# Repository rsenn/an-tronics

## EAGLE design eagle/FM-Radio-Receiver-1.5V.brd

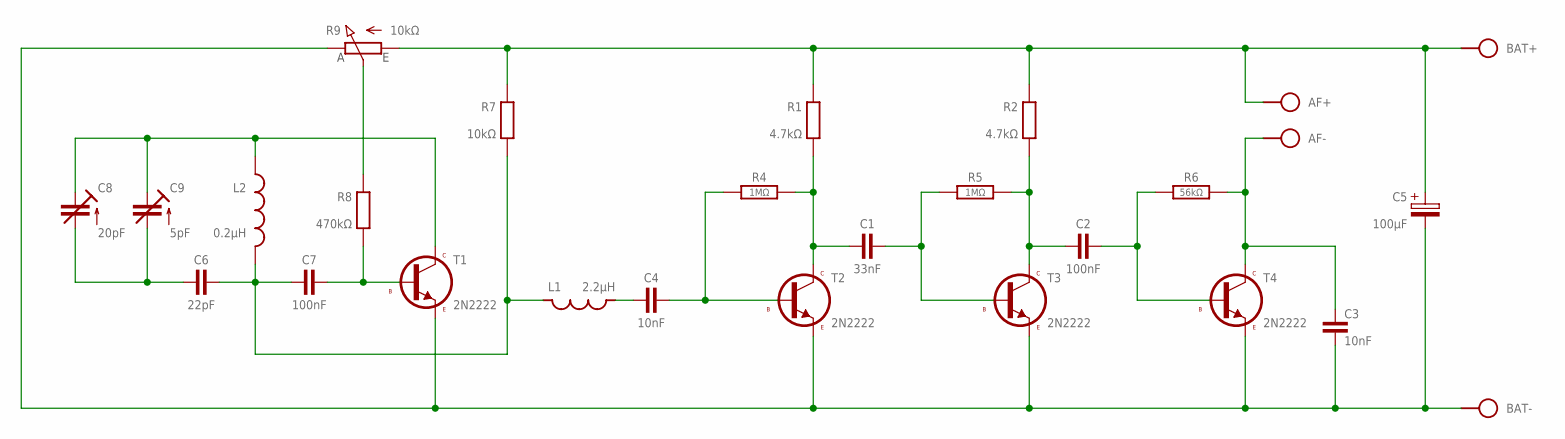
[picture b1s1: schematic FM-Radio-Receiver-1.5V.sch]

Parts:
AF: SPAD+-+-; SPAD+-
BAT: SPAD+-+-; SPAD+-
C1: 33nF; C050-020X044
C2: 100nF; C050-020X044
C3: 10nF; C050-025X060
C4: 10nF; C050-020X044
C5: 100μF; E2.5-4/V
C6: 22pF; C050-020X036
C7: 100nF; C075-020X044
C8: 20pF; TRIM-2222-808
C9: 5pF; CTRIMTZ03
L1: 2.2μH; L-03/10
L2: 0.2μH; L-10/10Y
R1, R2: 4.7kΩ; 0204/10-V
R4, R5: 1MΩ; 0204/10-V
R6: 56kΩ; 0204/10-V
R7: 10kΩ; 0204/10-V
R8: 470kΩ; 0204/10-V
R9: 10kΩ; CONN-3P
T1, T2, T3, T4: 2N2222; TO92

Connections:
unnamed: C1.2, R5.1, T3.2 (B)
unnamed: C2.1, R2.2 (1), R5.2, T3.3 (C)
unnamed: C1.1, R1.2 (1), R4.2, T2.3 (C)
unnamed: C2.2, R6.1, T4.2 (B)
unnamed: AF.1, C3.1, R6.2, T4.3 (C)
unnamed: C4.2, R4.1, T2.2 (B)
unnamed: C4.1, L1.1
unnamed: AF.2, BAT.2, C5.+, R1.1 (2), R2.1 (2), R7.1 (2), R9.1 (A)
unnamed: C7.2, R8.2 (1), T1.2 (B)
unnamed: R8.1 (2), R9.2 (S)
unnamed: C8.3 (E), C9.2 (E), L2.P$1 (1), T1.3 (C)
unnamed: C6.2, C7.1, L1.2, L2.P$2 (2), R7.2 (1)
unnamed: C6.1, C8.2 (A), C9.1 (A)
unnamed: BAT.1, C3.2, C5.-, R9.3 (E), T1.1 (E), T2.1 (E), T3.1 (E), T4.1 (E)

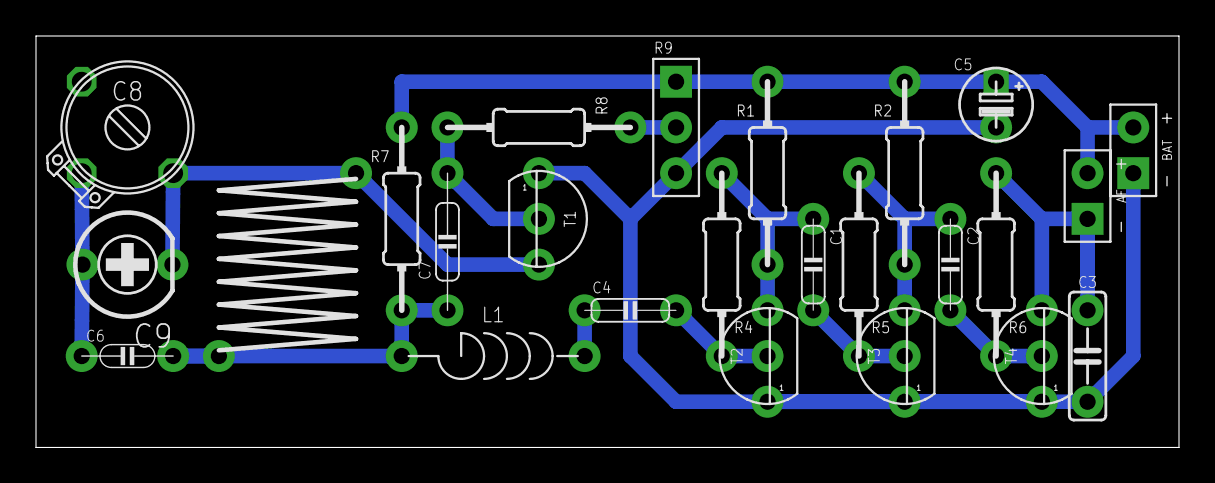
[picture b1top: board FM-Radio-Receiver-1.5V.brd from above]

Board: 2 copper layers, 63.5 x 22.9 mm, 25 parts (0 on the bottom side), 14 nets.

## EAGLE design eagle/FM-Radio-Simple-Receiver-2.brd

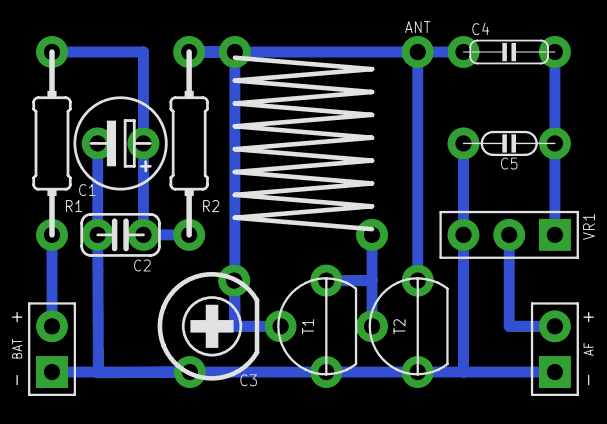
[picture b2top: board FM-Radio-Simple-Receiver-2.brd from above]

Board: 2 copper layers, 14 parts (0 on the bottom side), 7 nets.

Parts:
AF: SPAD+-+-; SPAD+-
ANT: ANT; SPAD
BAT: VCC_GNDL; SPAD-+
C1: 100µF; E2,5-5/V
C2: 100nF; C025-024X044
C3: 2 - 20pF; CTRIMBB
C4: 220nF; C050-020X044
C5: 2.2nF; C050-020X036/V
L1: 200nH; L-10/10X
R1: 1kΩ; 0204/10-V
R2: 10kΩ; 0204/10-V
T1, T2: 2N2222-A; TO92-A
VR1: 10kΩ; CONN-3P

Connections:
GND: AF.1, BAT.1, C1.-, C2.2, C3.1, C5.2, T1.1, T2.1, VR1.3
unnamed: ANT.1, C3.2, C4.1, L1.1, R2.2, T1.2, T2.3
unnamed: C1.+, C2.1, R1.2, R2.1
unnamed: C4.2, C5.1, VR1.1
unnamed: L1.2, T1.3, T2.2
unnamed: AF.2, VR1.2
VCC: BAT.2, R1.1

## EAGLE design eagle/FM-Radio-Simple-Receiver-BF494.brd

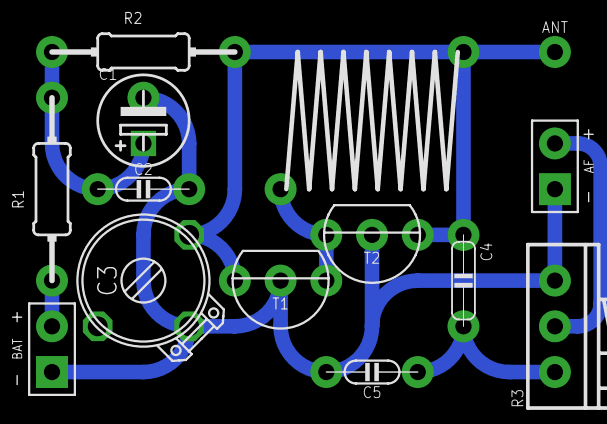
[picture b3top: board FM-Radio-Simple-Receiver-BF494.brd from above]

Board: 2 copper layers, 14 parts (0 on the bottom side), 7 nets.

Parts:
AF: SPAD+-+-; SPAD+-
ANT: ANT; SPAD
BAT: VCC_GNDL; SPAD-+
C1: 100µF; E2,5-5/V
C2: 100nF; C050-020X036/V
C3: 2 - 20pF; TRIM-2222-808
C4: 220nF; C050-020X044
C5: 2.2nF; C050-020X036/V
L1: 0.2µH; L-10/10X
R1: 1kΩ; 0204/10
R2: 10kΩ; 0204/10
R3: 10kΩ; POT
T1, T2: BF494; TO92-CEB

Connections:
GND: AF.1, BAT.1, C1.-, C2.2, C3.2, C5.2, R3.E, T1.E, T2.E
unnamed: ANT.1, C3.3, C4.1, L1.P$1, R2.2, T1.B, T2.C
unnamed: C1.+, C2.1, R1.2, R2.1
unnamed: C4.2, C5.1, R3.A
unnamed: L1.P$2, T1.C, T2.B
unnamed: AF.2, R3.S
VCC: BAT.2, R1.1

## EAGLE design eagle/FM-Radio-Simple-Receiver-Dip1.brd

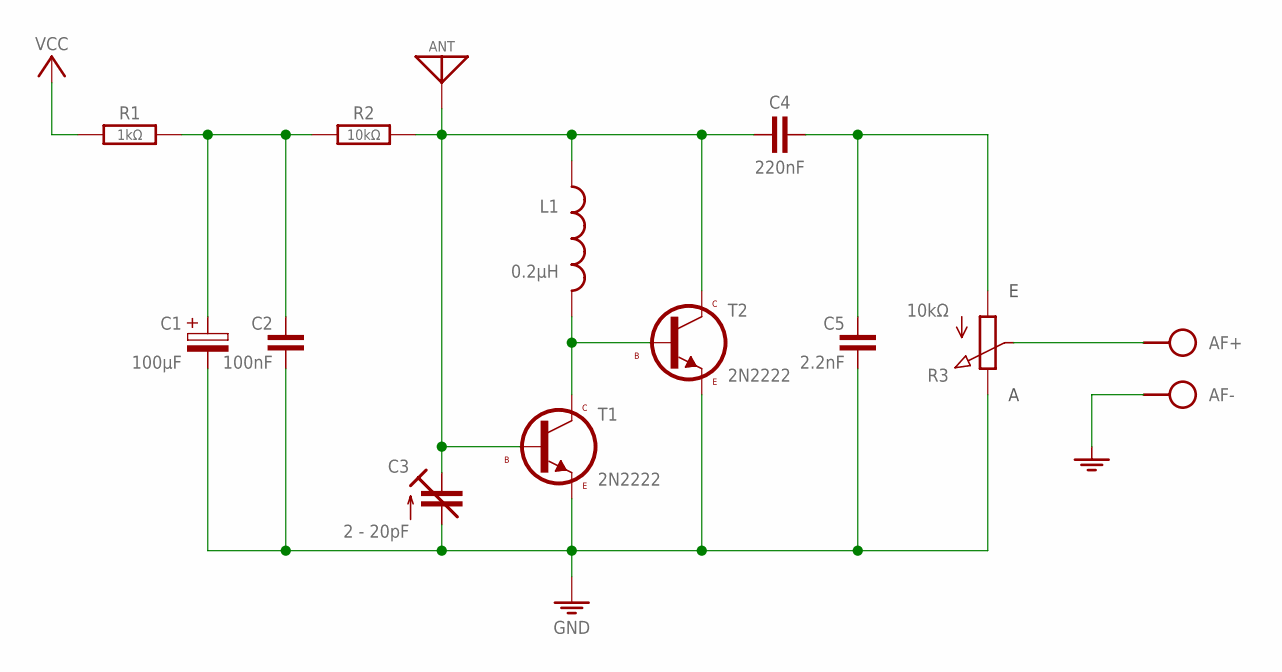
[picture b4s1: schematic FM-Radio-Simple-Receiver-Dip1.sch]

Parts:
AF: SPAD+--+; SPAD-+
ANT: ANT; SPAD
BAT: VCC_GNDL; SPAD-+
C1: 100µF; E2,5-5/V
C2: 100nF; C050-020X036/V
C3: 2 - 20pF; TRIM-2222-808
C4: 220nF; C050-020X044
C5: 2.2nF; C050-020X036/V
L1: 0.2µH; L-10/10Y
R1: 1kΩ; 0204/10
R2: 10kΩ; 0204/10
R3: 10kΩ; CONN-3P
T1, T2: 2N2222; TO92

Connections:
GND: AF.1, BAT.1 (GND), C1.-, C2.2, C3.2 (A), C5.2, R3.3 (E), T1.1 (E), T2.1 (E)
unnamed: ANT.1, C3.3 (E), C4.1, L1.P$1 (1), R2.2, T1.2 (B), T2.3 (C)
unnamed: C1.+, C2.1, R1.2, R2.1
unnamed: C4.2, C5.1, R3.1 (A)
unnamed: L1.P$2 (2), T1.3 (C), T2.2 (B)
unnamed: AF.2, R3.2 (S)
VCC: BAT.2 (VCC), R1.1

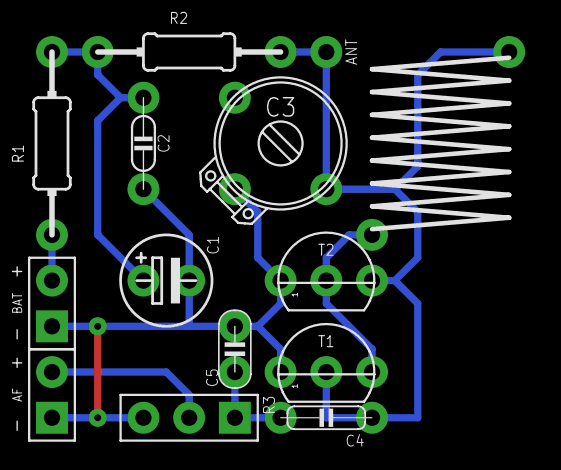
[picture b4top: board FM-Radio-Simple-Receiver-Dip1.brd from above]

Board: 2 copper layers, 14 parts (0 on the bottom side), 7 nets.
